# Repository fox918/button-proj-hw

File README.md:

# Hacker Jeopardy Buttons and Mood Lighting Shelf

## Idea

This is a small PCB designed for a NodeMCU v3 to control up to 4 WS2812b LED-Strips.
The goal of the project is to light up hacker jeopardy buttons or to light something with
the ws2812b buttons.

## Considerations:
- care has been taken that at least 2 strips are usable for Lua or Micropython respectively
- There is a jumper to bypass the voltage regulator if the board is directly supplied with 5V

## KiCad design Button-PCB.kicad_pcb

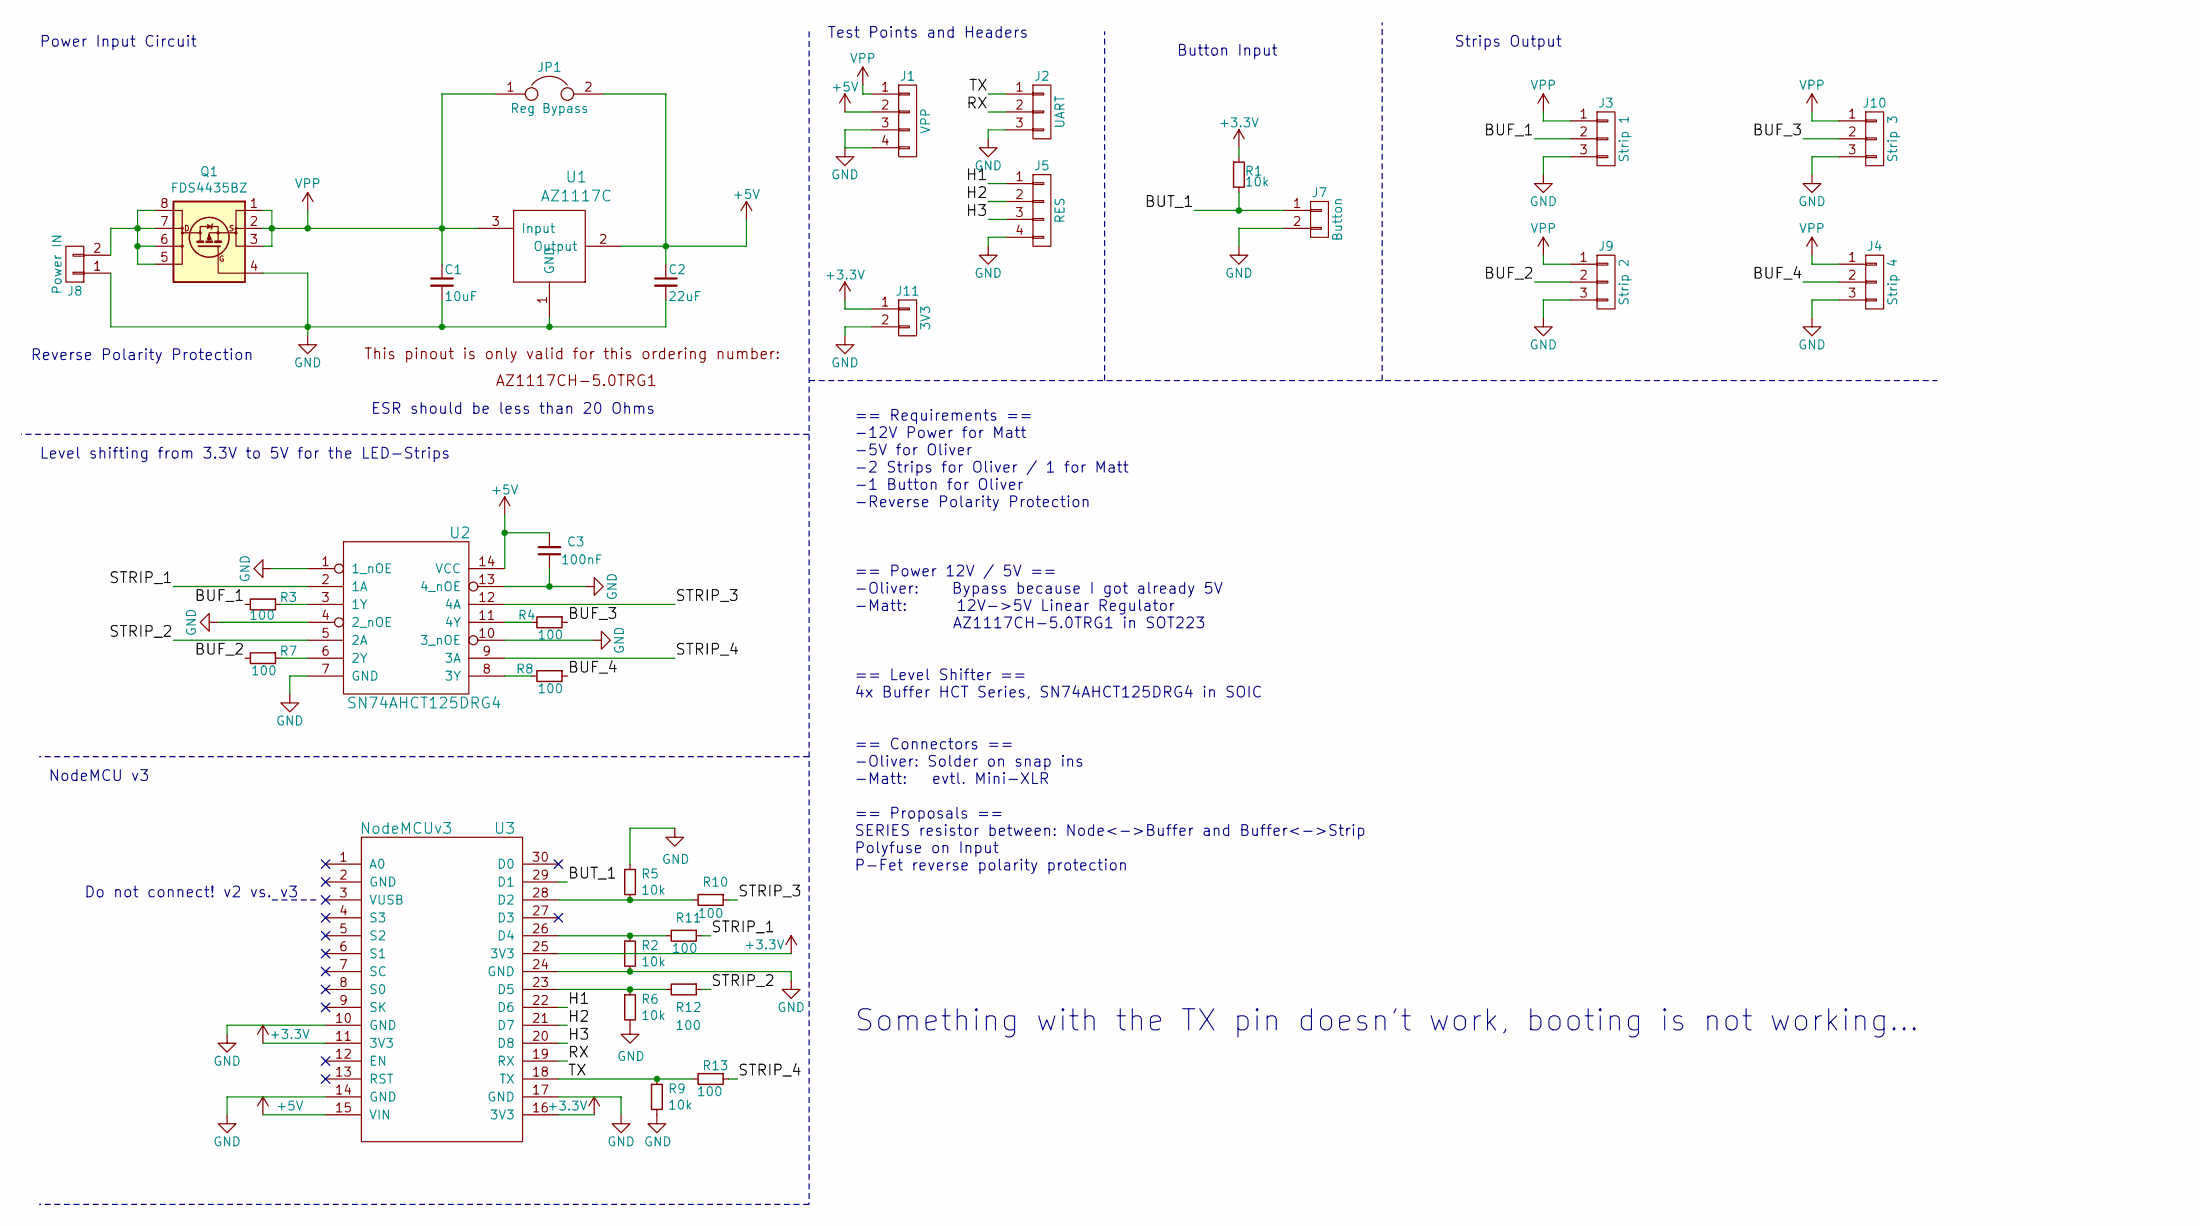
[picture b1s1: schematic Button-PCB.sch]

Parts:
C1: 10uF; C_0805
C2: 22uF; C_0805
C3: 100nF; C_0805
J1: VPP; Pin_Header_Straight_1x04_Pitch2.54mm
J2: UART; Pin_Header_Straight_1x03_Pitch2.54mm
J3: Strip 1; Pin_Header_Angled_1x03_Pitch2.54mm
J4: Strip 4; Pin_Header_Angled_1x03_Pitch2.54mm
J5: RES; Pin_Header_Straight_1x04_Pitch2.54mm
J7: Button; Pin_Header_Straight_1x02_Pitch2.54mm
J8: Power IN; Pin_Header_Straight_1x02_Pitch2.54mm
J9: Strip 2; Pin_Header_Angled_1x03_Pitch2.54mm
J10: Strip 3; Pin_Header_Angled_1x03_Pitch2.54mm
J11: 3V3; Pin_Header_Straight_1x02_Pitch2.54mm
JP1: Reg Bypass; Pin_Header_Straight_1x02_Pitch2.54mm
Q1: FDS4435BZ; SOIC-8_3.9x4.9mm_Pitch1.27mm
R1, R2, R5, R6, R9: 10k; R_0805
R3, R4, R7, R8, R10, R11, R12, R13: 100; R_0805
U1: AZ1117C; SOT-223-3Lead_TabPin2
U2: SN74AHCT125DRG4; SOIC-14_N
U3: NodeMCUv3; nodemcu_v3

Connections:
+3V3: J11.1, R1.1, U3.11 (3V3), U3.16 (3V3), U3.25 (3V3)
+5V: C2.1, C3.2, J1.2, JP1.2, U1.2 (Output), U2.14 (VCC), U3.15 (VIN)
/BUF_1: J3.2, R3.2
/BUF_2: J9.2, R7.2
/BUF_3: J10.2, R4.1
/BUF_4: J4.2, R8.1
/BUT_1: J7.1, R1.2, U3.29 (D1)
/H1: J5.1, U3.22 (D6)
/H2: J5.2, U3.21 (D7)
/H3: J5.3, U3.20 (D8)
/RX: J2.2, U3.19 (RX)
/STRIP_1: R11.1, U2.2 (1A)
/STRIP_2: R12.1, U2.5 (2A)
/STRIP_3: R10.1, U2.12 (4A)
/STRIP_4: R13.1, U2.9 (3A)
/TX: J2.1, R9.1, R13.2, U3.18 (TX)
GND: C1.2, C2.2, C3.1, J1.3, J1.4, J2.3, J3.3, J4.3, J5.4, J7.2, J8.1, J9.3, J10.3, J11.2, Q1.4 (G), R2.2, R5.1, R6.2, R9.2, U1.1 (GND), U2.1 (1_nOE), U2.4 (2_nOE), U2.7 (GND), U2.10 (3_nOE), U2.13 (4_nOE), U3.10 (GND), U3.14 (GND), U3.17 (GND), U3.24 (GND)
unnamed: J8.2, Q1.5 (D), Q1.6 (D), Q1.7 (D), Q1.8 (D)
unnamed: R3.1, U2.3 (1Y)
unnamed: R4.2, U2.11 (4Y)
unnamed: R7.1, U2.6 (2Y)
unnamed: R8.2, U2.8 (3Y)
unnamed: R5.2, R10.2, U3.28 (D2)
unnamed: R2.1, R11.2, U3.26 (D4)
unnamed: R6.1, R12.2, U3.23 (D5)
VPP: C1.1, J1.1, J3.1, J4.1, J9.1, J10.1, JP1.1, Q1.1 (S), Q1.2 (S), Q1.3 (S), U1.3 (Input)

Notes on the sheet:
== Requirements == -12V Power for Matt -5V for Oliver -2 Strips for Oliver / 1 for Matt -1 Button for Oliver -Reverse Polarity Protection == Power 12V / 5V == -Oliver: Bypass because I got already 5V -Matt: 12V->5V Linear Regulator AZ1117CH-5.0TRG1 in SOT223 == Level Shifter == 4x Buffer HCT Series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
Strips Output
Button Input
Test Points and Headers
ESR should be less than 20 Ohms
Power Input Circuit
Do not connect! v2 vs. v3
Reverse Polarity Protection
Level shifting from 3.3V to 5V for the LED-Strips
NodeMCU v3
Something with the TX pin doesn't work, booting is not working...

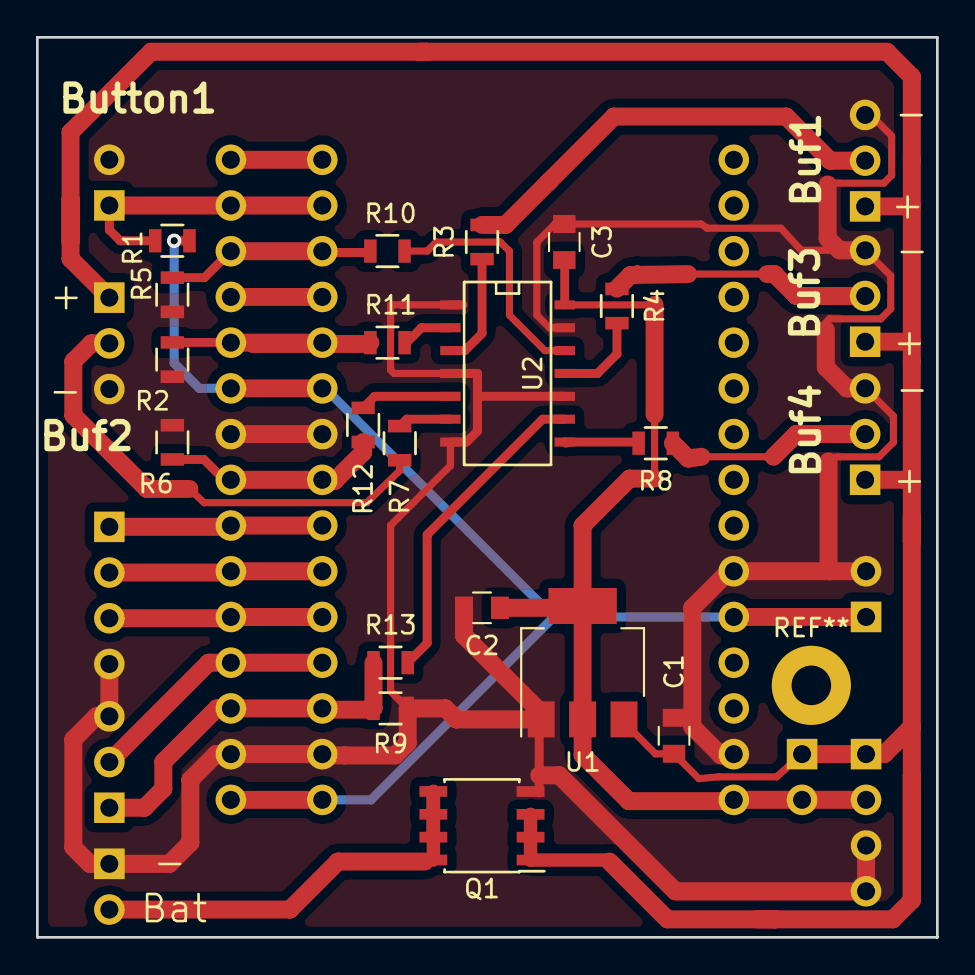
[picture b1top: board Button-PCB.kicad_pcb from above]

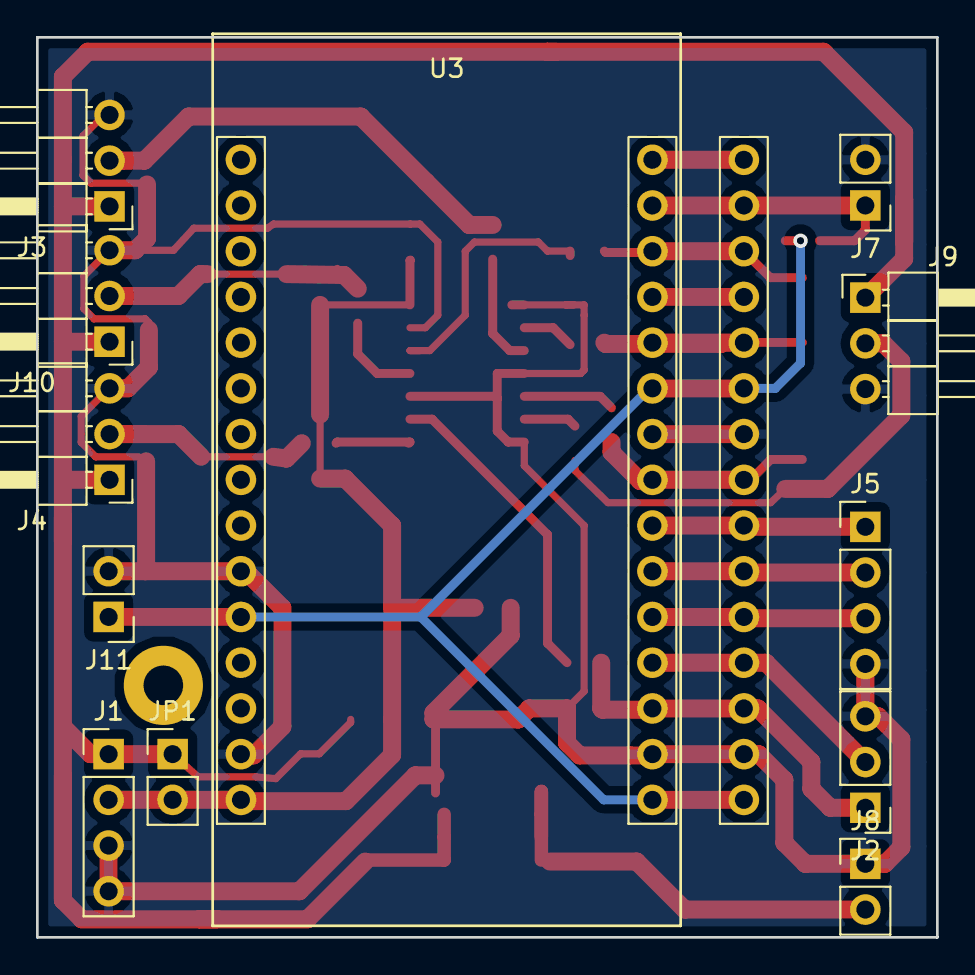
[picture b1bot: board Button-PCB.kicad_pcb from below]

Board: 2 copper layers, 50.0 x 50.0 mm, 31 parts (12 on the bottom side), 26 nets.

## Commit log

2017-06-15 readme
2017-06-15 deleted wrong readme
2017-06-15 added a few sentences to the readme
2017-06-17 Removing note on caps for the nodemcu
    Caps are probably not required across the rails of the nodemcu because:
    1. The capacitor at the output of the regulator takes care of some
    decoupling already.
    2. There's probably a sufficient amount of capacitance on the nodemcu
    board already.
2017-06-17 Stop tracking Button-PCB.bak file
2017-06-17 Adding missing wire between STRIP label and termination resistors.
2017-06-17 Adding 100k pull-down resistors to buffer input.
2017-06-17 Moving series termination resistors from sink (buf) to source (esp)
2017-06-17 Value of series termination resistors: 100R
2017-06-17 Reducing pull-down resistor values from 100k to 10k
    A 10k resistor is already used as pull-up for the button. This change
    keeps the number of distinct resistor values low.
2017-06-17 Moving series termination of strips to source and assigning 100R
2017-06-17 Minor schematic rework to tie up loose ends. No functional changes.
2017-06-17 Initial part annotation
2017-06-17 Assigning footprints for resistors (0805), caps (0805) and buffer (SOIC-N)
2017-06-17 Swap out FDS4435BZ symbol with one of the correct pinout for the SOIC-8 footprint.
2017-06-17 Adding GND pin to UART and RES connectors.
2017-06-17 Using standard 2.54" headers for all connectors for now. Will change later.
2017-06-18 Initial version of NodeMCU footprint. Unchecked!
    With 3d model of socket strips, rough outline and fp-lib-table entry.
2017-06-18 Fixing pin numbering in NodeMCU footprint.
2017-06-18 Assigning NodeMCU footprint
2017-06-18 Stop tracking nodemcuv3.bak file
2017-06-18 AZ1117CH-5.0TRG1 symbol fix: Swapped GND pin number and name.
2017-06-18 Swapping STRIP_2 and STRIP_4 nodes for easier routing
2017-06-18 Relocating pull-down resistors for easier routing
2017-06-24 Fixed assignment of footprint for AZ1117C part.
2017-06-24 Annotate regulator (U1)
2017-06-27 Rename nets so that strip 3 drives buf 3 instead of buf 4.
2017-08-03 Initial board layout. Very crude, see ticket for necessary changes.
2017-11-17 hacking bugs
